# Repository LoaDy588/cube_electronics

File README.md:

# Cube Electronics

## Content

The repo currently contains KiCAD source files for the main board, interface board and a tiny sensor head.
It also includes all accompanying files, such as BOM.

## Building

The supplied `makefile` uses [KiKit](https://github.com/yaqwsx/KiKit) to automatically generate all output gerber files for JLCPCB.
Just run `make` in the top level directory to create all output gerbers and zip them in the `./gerber/` folder.

## 3D models, schematic symbols, footprints

This project relies on [LoaDy KiCAD Libs](https://github.com/LoaDy588/LoaDy_KiCAD_libs) for some footprints and the 3D models in the 3D preview on PCBNew

## License

The Main Board and Interface Board are licensed under CERN-OHL-W v2.

The MLX90393 sensor head is not licensed at all.

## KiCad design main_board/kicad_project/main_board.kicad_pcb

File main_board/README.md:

# Main Board

This is the main control board for Cube.

## Features
- powered by STM32G4 170MHz Cortex-M4 MCU
- four independent TMC2209 stepper drivers
- fully protected 10x limit switch inputs capable of 12V input
- USB communication with PC
- I2C and UART passthrough to MCU
- 3V3, 5V and 12V(supply) power rails

## License

Copyright Oldřich Pecák 2020.

This source describes Open Hardware and is licensed under the CERN-OHL-W v2.

You may redistribute and modify this source and make products using it under the terms of the CERN-OHL-S v2 (https://ohwr.org/cern_ohl_w_v2.txt).

This source is distributed WITHOUT ANY EXPRESS OR IMPLIED WARRANTY, INCLUDING OF MERCHANTABILITY, SATISFACTORY QUALITY AND FITNESS FOR A PARTICULAR PURPOSE. Please see the CERN-OHL-W v2 for applicable conditions.

Source location: LICENSE.txt

As per CERN-OHL-W v2 section 4, should You produce hardware based on this source, You must where practicable maintain the Source Location visible on the external case of the Gizmo or other products you make using this source.

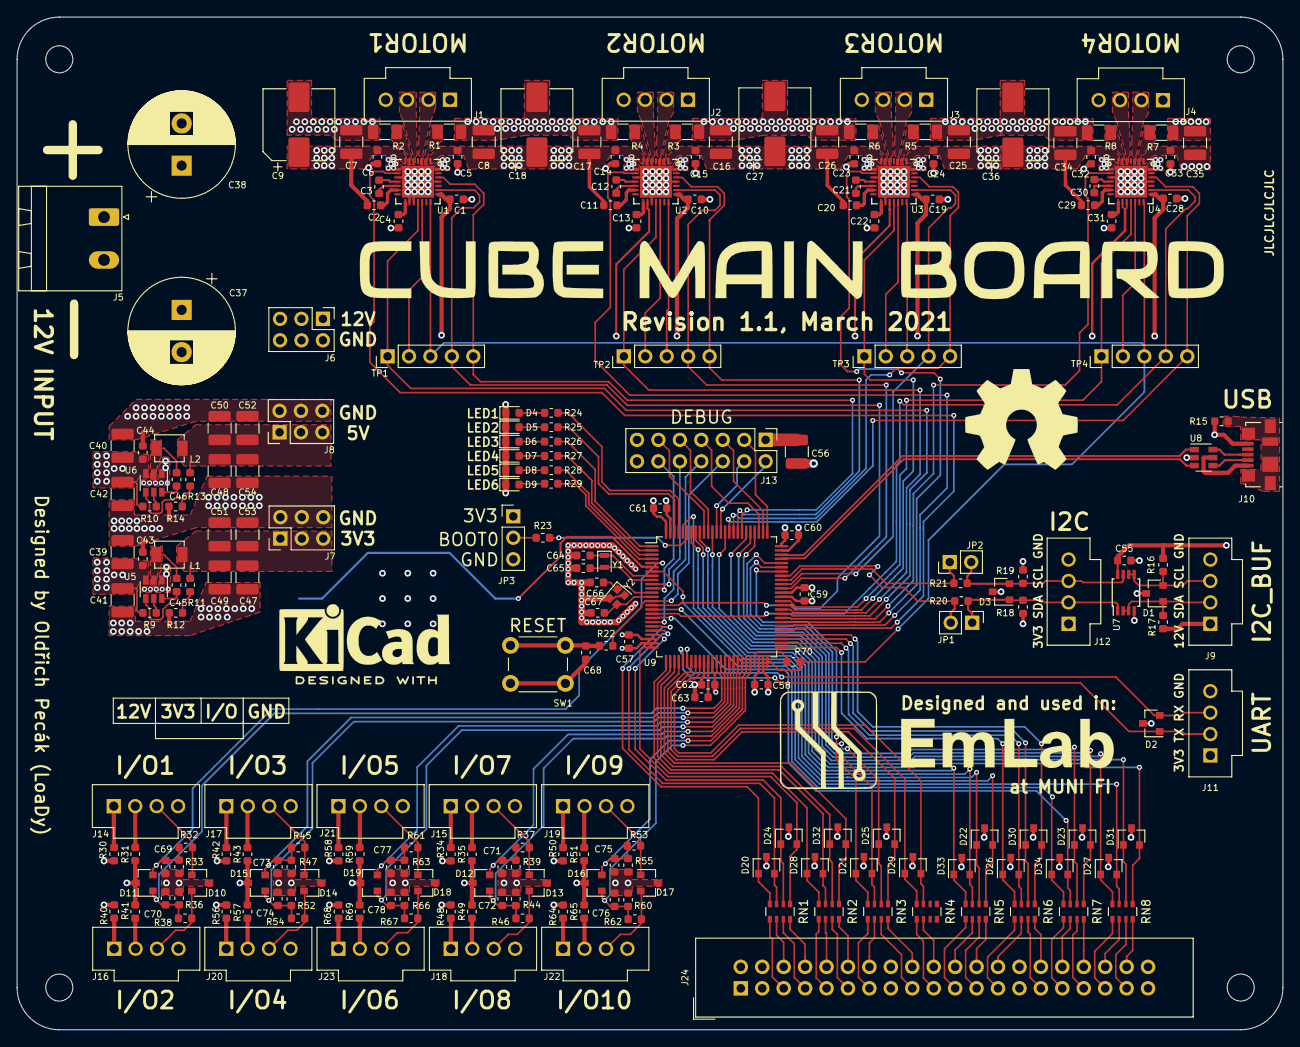
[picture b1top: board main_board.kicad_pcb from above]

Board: 4 copper layers, 150.0 x 120.0 mm, 236 parts (1 on the bottom side), 220 nets.

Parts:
BT1: CR2032; CR2032_SMD
C1, C2, C5, C6, C10, C11, C14, C15, C19, C20, C23, C24, C28, C29, C32, C33, C43, C44, C45, C46, C55, C57, C58, C59, C60, C61, C62, C63, C68: 100n; C_0603_1608Metric
C3, C12, C21, C30: 22n; C_0603_1608Metric
C4, C13, C22, C31: 2u2; C_0603_1608Metric
C7, C8, C16, C17, C25, C26, C34, C35, C39, C40, C41, C42, C47, C48, C49, C50, C51, C52, C53, C54, C56: 10u; C_1210_3225Metric
C9, C18, C27, C36: 100u; CP_Elec_8x10
C37, C38: 1m; CP_Radial_D12.5mm_P5.00mm
C64, C65: 12p5; C_0603_1608Metric
C66, C67: DNP; C_0603_1608Metric
C69, C70, C71, C72, C73, C74, C75, C76, C77, C78: 2n2; C_0603_1608Metric
D1: PESD12VS2UT; SOT-23
D2, D3, D10, D13, D14, D17, D18, D20, D21, D22, D23, D24, D25, D26, D27, D28, D29, D30, D31, D32, D33, D34: PESD3V3S2UT; SOT-23
D4, D5: LED_R; D_0603_1608Metric
D6, D7: LED_O; D_0603_1608Metric
D8, D9: LED_G; D_0603_1608Metric
D11, D12, D15, D16, D19: BAT54C; SOT-23
J1, J2, J3, J4: MOTOR; Molex_70543-0003
J5: PWR_ENTRY; PhoenixContact_MSTBA_2,5_2-G-5,08_1x02_P5.08mm_Horizontal
J6: 12V_HDR; PinHeader_2x03_P2.54mm_Vertical
J7: 3V3_HDR; PinHeader_2x03_P2.54mm_Vertical
J8: 5V_HDR; PinHeader_2x03_P2.54mm_Vertical
J9: I2C_BUFFERED; Molex_70543-0003
J10: USB_B_Micro; USB_Micro-B_Molex_47346-0001
J11: DATA_UART; Molex_70543-0003
J12: I2C_EXTERNAL; Molex_70543-0003
J13: DEBUG_HEADER; PinHeader_2x07_P2.54mm_Vertical
J14: IO1; Molex_70543-0003
J15: IO7; Molex_70543-0003
J16: IO2; Molex_70543-0003
J17: IO3; Molex_70543-0003
J18: IO8; Molex_70543-0003
J19: IO9; Molex_70543-0003
J20: IO4; Molex_70543-0003
J21: IO5; Molex_70543-0003
J22: IO10; Molex_70543-0003
J23: IO6; Molex_70543-0003
J24: EXPANSION_HEADER; IDC-Header_2x20_P2.54mm_Vertical
JP1: SDA_JMP; PinHeader_1x02_P2.54mm_Vertical
JP2: SCL_JMP; PinHeader_1x02_P2.54mm_Vertical
JP3: BOOT_SELECT; PinHeader_1x03_P2.54mm_Vertical
L1: 3u3; BOURNS_SRP3020TA
L2: 4u7; BOURNS_SRP3020TA
R1, R2, R3, R4, R5, R6, R7, R8: 150m; R_1206_3216Metric
R9, R10, R12, R14: 10K; R_0603_1608Metric
R11: 33K2; R_0603_1608Metric
R13: 54K9; R_0603_1608Metric
R15: 1M; R_0603_1608Metric
R16, R17: 2K2; R_0603_1608Metric
R18, R19, R32, R37, R38, R45, R46, R53, R54, R61, R62, R67: 4K7; R_0603_1608Metric
R20, R21: 0R; R_0603_1608Metric
R22: 150R; R_0603_1608Metric
R23, R24, R25, R26, R27, R28, R29, R30, R31, R34, R35, R40, R41, R42, R43, R48, R49, R50, R51, R56, R57, R58, R59, R64, R65, R68, R69, R70: 1K; R_0603_1608Metric
R33, R36, R39, R44, R47, R52, R55, R60, R63, R66: 47K; R_0603_1608Metric
RN1, RN2, RN3, RN4, RN5, RN6, RN7, RN8: 150R; R_Array_Convex_4x0603
SW1: SW_SPST; SW_PUSH_6mm_H5mm
TP1, TP2, TP3, TP4: DRIVER_TP; PinHeader_1x05_P2.54mm_Vertical
U1, U2, U3, U4: TMC2209; TMC2209-LA
U5, U6: TPS562200; SOT-23-6
U7: PCA9600DP; TSSOP-8_3x3mm_P0.65mm
U8: USBLC6-2SC6; SOT-23-6
U9: STM32G474VxT; LQFP-100_14x14mm_P0.5mm
Y1: ABS06-32.768kHz; Crystal_SMD_2012-2Pin_2.0x1.2mm
Y2: DNP; Crystal_SMD_2016-4Pin_2.0x1.6mm

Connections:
+3V3: C1.2, C10.2, C19.2, C28.2, C47.1, C49.1, C51.1, C53.1, C56.2, C57.2, C58.2, C59.2, C60.2, C61.2, C62.2, D11.3, D12.3, D15.3, D16.3, D19.3, J7.1, J7.3, J7.5, J11.1, J12.1, J13.1, J24.3, J24.4, JP3.1, L1.2, R11.1, R18.2, R19.2, R31.1, R35.1, R41.1, R43.1, R49.1, R51.1, R57.1, R59.1, R65.1, R69.1, U1.15, U2.9, U2.15, U3.10, U3.15, U4.9, U4.10, U4.15, U9.24, U9.37, U9.49, U9.64, U9.75, U9.100
+5V: C48.1, C50.1, C52.1, C54.1, J8.1, J8.3, J8.5, L2.2, R13.1
+12V: C2.2, C5.1, C6.1, C7.1, C8.1, C9.1, C11.2, C14.1, C15.1, C16.1, C17.1, C18.1, C20.2, C23.1, C24.1, C25.1, C26.1, C27.1, C29.2, C32.1, C33.1, C34.1, C35.1, C36.1, C37.1, C38.1, C39.1, C40.1, C41.1, C42.1, C43.1, C44.1, C55.1, J5.1, J6.1, J6.3, J6.5, J9.1, J24.1, J24.2, R9.2, R10.2, R16.2, R17.2, R30.1, R34.1, R40.1, R42.1, R48.1, R50.1, R56.1, R58.1, R64.1, R68.1, U1.22, U1.28, U2.22, U2.28, U3.22, U3.28, U4.22, U4.28, U5.3, U6.3, U7.8
/External I/O/DATA_UART_RX: D2.2, J11.3, U9.31
/External I/O/DATA_UART_TX: D2.1, J11.2, U9.30
/External I/O/I2C_SCL: JP2.1, R21.2, U9.67
/External I/O/I2C_SDA: JP1.2, R20.2, U9.68
/External I/O/USB_DATA_N: U8.3, U9.72
/External I/O/USB_DATA_P: U8.1, U9.73
/Limit Switches/IO1: C69.1, D11.2, R32.1, R33.2, U9.5
/Limit Switches/IO2: C70.2, D11.1, R36.2, R38.1, U9.38
/Limit Switches/IO3: C73.1, D15.2, R45.1, R47.2, U9.39
/Limit Switches/IO4: C74.2, D15.1, R52.2, R54.1, U9.40
/Limit Switches/IO5: C77.1, D19.2, R61.1, R63.2, U9.41
/Limit Switches/IO6: C78.2, D19.1, R66.2, R67.1, U9.42
/Limit Switches/IO7: C71.1, D12.2, R37.1, R39.2, U9.43
/Limit Switches/IO8: C72.2, D12.1, R44.2, R46.1, U9.44
/Limit Switches/IO9: C75.1, D16.2, R53.1, R55.2, U9.45
/Limit Switches/IO10: C76.2, D16.1, R60.2, R62.1, U9.46
/MCU/32_OSC_IN: C64.2, U9.8, Y1.1
/MCU/32_OSC_OUT: C65.2, U9.9, Y1.2
/MCU/BOOT0: R23.2, U9.95
/MCU/DEBUG_GPIO1: J13.8, U9.19
/MCU/DEBUG_GPIO2: J13.10, U9.10
/MCU/DEBUG_GPIO3: J13.12, U9.11
/MCU/DEBUG_LED1: R24.2, U9.97
/MCU/DEBUG_LED2: R25.2, U9.98
/MCU/DEBUG_LED3: R26.2, U9.1
/MCU/DEBUG_LED4: R27.2, U9.2
/MCU/DEBUG_LED6: R29.2, U9.4
/MCU/DEBUG_UART_RX: J13.4, U9.88
/MCU/DEBUG_UART_TX: J13.2, U9.87
/MCU/DEUBG_LED5: R28.2, U9.3
/MCU/EXP_IO1: D20.1, RN1.4, U9.20
/MCU/EXP_IO2: D20.2, RN1.3, U9.21
/MCU/EXP_IO3: D24.1, RN1.2, U9.22
/MCU/EXP_IO4: D24.2, RN1.1, U9.25
/MCU/EXP_IO5: D28.1, RN2.4, U9.26
/MCU/EXP_IO6: D28.2, RN2.3, U9.27
/MCU/EXP_IO7: D32.1, RN2.2, U9.28
/MCU/EXP_IO8: D32.2, RN2.1, U9.29
/MCU/EXP_IO9: D21.1, RN3.4, U9.69
/MCU/EXP_IO10: D21.2, RN3.3, U9.70
/MCU/EXP_IO11: D25.1, RN3.2, U9.71
/MCU/EXP_IO12: D25.2, RN3.1, U9.32
/MCU/EXP_IO13: D29.1, RN4.4, U9.33
/MCU/EXP_IO14: D29.2, RN4.3, U9.34
/MCU/EXP_IO15: D33.1, RN5.4, U9.92
/MCU/EXP_IO16: D33.2, RN5.3, U9.93
/MCU/EXP_IO17: D22.1, RN5.2, U9.94
/MCU/EXP_IO18: D22.2, RN5.1, U9.96
/MCU/EXP_IO19: D26.1, RN6.4, U9.51
/MCU/EXP_IO20: D26.2, RN6.3, U9.52
/MCU/EXP_IO21: D30.1, RN6.2, U9.53
/MCU/EXP_IO22: D30.2, RN6.1, U9.54
/MCU/EXP_IO23: D34.1, RN7.4, U9.16
/MCU/EXP_IO24: D34.2, RN7.3, U9.18
/MCU/EXP_IO25: D23.1, RN7.2, U9.79
/MCU/EXP_IO26: D23.2, RN7.1, U9.80
/MCU/EXP_IO27: D27.1, RN8.4, U9.81
/MCU/EXP_IO28: D27.2, RN8.3, U9.7
/MCU/EXP_IO29: D31.1, RN8.2, U9.86
/MCU/EXP_IO30: D31.2, RN8.1, U9.89
/MCU/HS_OSC_IN: C66.2, U9.12, Y2.1
/MCU/HS_OSC_OUT: C67.2, U9.13, Y2.3
/MCU/JDI: J13.7, U9.78
/MCU/JTDO_TRACESWO: J13.9, U9.90
/MCU/JTRST: J13.11, U9.91
/MCU/NRST: J13.6, R22.2, U9.14
/MCU/STEP_UART_RX: R70.2, TP1.3, TP2.3, TP3.3, TP4.3, U1.14, U2.14, U3.14, U4.14, U9.50
/MCU/STEP_UART_TX: R70.1, U9.47
/MCU/SWCLK_JTCK: J13.5, U9.77
/MCU/SWDIO_JTMS: J13.3, U9.76
/MCU/VREF: C63.2, U9.36
/STEP1/DIAG: TP1.1, U1.11, U9.59
/STEP1/DIR: TP1.5, U1.19, U9.82
/STEP1/ENABLE: U1.2, U9.55
/STEP1/INDEX: TP1.2, U1.12
/STEP1/STEP: TP1.4, U1.16, U9.15
/STEP2/DIAG: TP2.1, U2.11, U9.60
/STEP2/DIR: TP2.5, U2.19, U9.83
/STEP2/ENABLE: U2.2, U9.56
/STEP2/INDEX: TP2.2, U2.12
/STEP2/STEP: TP2.4, U2.16, U9.65
/STEP3/DIAG: TP3.1, U3.11, U9.61
/STEP3/DIR: TP3.5, U3.19, U9.84
/STEP3/ENABLE: U3.2, U9.57
/STEP3/INDEX: TP3.2, U3.12
/STEP3/STEP: TP3.4, U3.16, U9.66
/STEP4/DIAG: TP4.1, U4.11, U9.62
/STEP4/DIR: TP4.5, U4.19, U9.85
/STEP4/ENABLE: U4.2, U9.58
/STEP4/INDEX: TP4.2, U4.12
/STEP4/STEP: TP4.4, U4.16, U9.17
GND: BT1.2, C1.1, C4.2, C5.2, C6.2, C7.2, C8.2, C9.2, C10.1, C13.2, C14.2, C15.2, C16.2, C17.2, C18.2, C19.1, C22.2, C23.2, C24.2, C25.2, C26.2, C27.2, C28.1, C31.2, C32.2, C33.2, C34.2, C35.2, C36.2, C37.2, C38.2, C39.2, C40.2, C41.2, C42.2, C43.2, C44.2, C47.2, C48.2, C49.2, C50.2, C51.2, C52.2, C53.2, C54.2, C55.2, C56.1, C57.1, C58.1, C59.1, C60.1, C61.1, C62.1, C63.1, C64.1, C65.1, C66.1, C67.1, C68.1, C69.2, C70.1, C71.2, C72.1, C73.2, C74.1, C75.2, C76.1, C77.2, C78.1, D1.3, D2.3, D3.3, D4.1, D5.1, D6.1, D7.1, D8.1, D9.1, D10.3, D13.3, D14.3, D17.3, D18.3, D20.3, D21.3, D22.3, D23.3, D24.3, D25.3, D26.3, D27.3, D28.3, D29.3, D30.3, D31.3, D32.3, D33.3, D34.3, J5.2, J6.2, J6.4, J6.6, J7.2, J7.4, J7.6, J8.2, J8.4, J8.6, J9.4, J10.5, J11.4, J12.4, J13.13, J13.14, J14.4, J15.4, J16.4, J17.4, J18.4, J19.4, J20.4, J21.4, J22.4, J23.4, J24.15, J24.16, J24.27, J24.28, J24.39, J24.40, JP3.3, R1.1, R2.1, R3.1, R4.1, R5.1, R6.1, R7.1, R8.1, R12.2, R14.2, R15.1, R33.1, R36.1, R39.1, R44.1, R47.1, R52.1, R55.1, R60.1, R63.1, R66.1, SW1.2, U1.3, U1.9, U1.10, U1.18, U1.29, U2.3, U2.10, U2.18, U2.29, U3.3, U3.9, U3.18, U3.29, U4.3, U4.18, U4.29, U5.1, U6.1, U7.4, U8.2, U9.23, U9.35, U9.48, U9.63, U9.74, U9.99, Y2.2, Y2.4
unnamed: BT1.1, U9.6
unnamed: C2.1, U1.6
unnamed: C3.1, U1.5
unnamed: C3.2, U1.4
unnamed: C4.1, U1.8
unnamed: C11.1, U2.6
unnamed: C12.1, U2.5
unnamed: C12.2, U2.4
unnamed: C13.1, U2.8
unnamed: C20.1, U3.6
unnamed: C21.1, U3.5
unnamed: C21.2, U3.4
unnamed: C22.1, U3.8
unnamed: C29.1, U4.6
unnamed: C30.1, U4.5
unnamed: C30.2, U4.4
unnamed: C31.1, U4.8
unnamed: C45.1, L1.1, U5.2
unnamed: C45.2, U5.6
unnamed: C46.1, L2.1, U6.2
unnamed: C46.2, U6.6
unnamed: C68.2, R22.1, SW1.1
unnamed: D1.1, J9.2, R17.1, U7.2, U7.3
unnamed: D1.2, J9.3, R16.1, U7.5, U7.6
unnamed: D3.1, J12.2, JP1.1, R18.1, R20.1, U7.1
unnamed: D3.2, J12.3, JP2.2, R19.1, R21.1, U7.7
unnamed: D4.2, R24.1
unnamed: D5.2, R25.1
unnamed: D6.2, R26.1
unnamed: D7.2, R27.1
unnamed: D8.2, R28.1
unnamed: D9.2, R29.1
unnamed: D10.1, J14.3, R32.2
unnamed: D10.2, J16.3, R38.2
unnamed: D13.1, J15.3, R37.2
unnamed: D13.2, J18.3, R46.2
unnamed: D14.1, J17.3, R45.2
unnamed: D14.2, J20.3, R54.2
unnamed: D17.1, J19.3, R53.2
unnamed: D17.2, J22.3, R62.2
unnamed: D18.1, J21.3, R61.2
unnamed: D18.2, J23.3, R67.2
unnamed: J1.1, U1.21
unnamed: J1.2, U1.24
unnamed: J1.3, U1.26
unnamed: J1.4, U1.1
unnamed: J2.1, U2.21
unnamed: J2.2, U2.24
unnamed: J2.3, U2.26
unnamed: J2.4, U2.1
unnamed: J3.1, U3.21
unnamed: J3.2, U3.24
unnamed: J3.3, U3.26
unnamed: J3.4, U3.1
unnamed: J4.1, U4.21
unnamed: J4.2, U4.24
unnamed: J4.3, U4.26
unnamed: J4.4, U4.1
unnamed: J10.1, U8.5
unnamed: J10.2, U8.4
unnamed: J10.3, U8.6
unnamed: J10.6, R15.2
unnamed: J14.1, R30.2
unnamed: J14.2, R31.2
unnamed: J15.1, R34.2
unnamed: J15.2, R35.2
unnamed: J16.1, R40.2
unnamed: J16.2, R41.2
unnamed: J17.1, R42.2
unnamed: J17.2, R43.2
unnamed: J18.1, R48.2
unnamed: J18.2, R49.2
unnamed: J19.1, R50.2
unnamed: J19.2, R51.2
unnamed: J20.1, R56.2
unnamed: J20.2, R57.2
unnamed: J21.1, R58.2
unnamed: J21.2, R59.2
unnamed: J22.1, R64.2
unnamed: J22.2, R65.2
unnamed: J23.1, R68.2
unnamed: J23.2, R69.2
unnamed: J24.5, RN1.5
unnamed: J24.6, RN1.6
unnamed: J24.7, RN1.7
unnamed: J24.8, RN1.8
unnamed: J24.9, RN2.5
unnamed: J24.10, RN2.6
unnamed: J24.11, RN2.7
unnamed: J24.12, RN2.8
unnamed: J24.13, RN3.5
unnamed: J24.14, RN3.6
unnamed: J24.17, RN3.7
unnamed: J24.18, RN3.8
unnamed: J24.19, RN4.5
unnamed: J24.20, RN4.6
unnamed: J24.21, RN5.5
unnamed: J24.22, RN5.6
unnamed: J24.23, RN5.7
unnamed: J24.24, RN5.8
unnamed: J24.25, RN6.5
unnamed: J24.26, RN6.6
unnamed: J24.29, RN6.7
unnamed: J24.30, RN6.8
unnamed: J24.31, RN7.5
unnamed: J24.32, RN7.6
unnamed: J24.33, RN7.7
unnamed: J24.34, RN7.8
unnamed: J24.35, RN8.5
unnamed: J24.36, RN8.6
unnamed: J24.37, RN8.7
unnamed: J24.38, RN8.8
unnamed: JP3.2, R23.1
unnamed: R1.2, U1.23
unnamed: R2.2, U1.27
unnamed: R3.2, U2.23
unnamed: R4.2, U2.27
unnamed: R5.2, U3.23
unnamed: R6.2, U3.27
unnamed: R7.2, U4.23
unnamed: R8.2, U4.27
unnamed: R9.1, U5.5
unnamed: R10.1, U6.5
unnamed: R11.2, R12.1, U5.4
unnamed: R13.2, R14.1, U6.4

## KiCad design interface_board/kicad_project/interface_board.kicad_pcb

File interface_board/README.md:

# Interface Board

This board serves as a sensor interface on the moving head.

It includes power regulators, GPIO and two communication busses - I2C and SPI.

It communicates with the main board via buffered 12V I2C bus.

## License

Copyright Oldřich Pecák 2020.

This source describes Open Hardware and is licensed under the CERN-OHL-W v2.

You may redistribute and modify this source and make products using it under the terms of the CERN-OHL-W v2 (https://ohwr.org/cern_ohl_w_v2.txt).

This source is distributed WITHOUT ANY EXPRESS OR IMPLIED WARRANTY, INCLUDING OF MERCHANTABILITY, SATISFACTORY QUALITY AND FITNESS FOR A PARTICULAR PURPOSE. Please see the CERN-OHL-W v2 for applicable conditions.

Source location: LICENSE.txt

As per CERN-OHL-W v2 section 4, should You produce hardware based on this source, You must where practicable maintain the Source Location visible on the external case of the Gizmo or other products you make using this source.

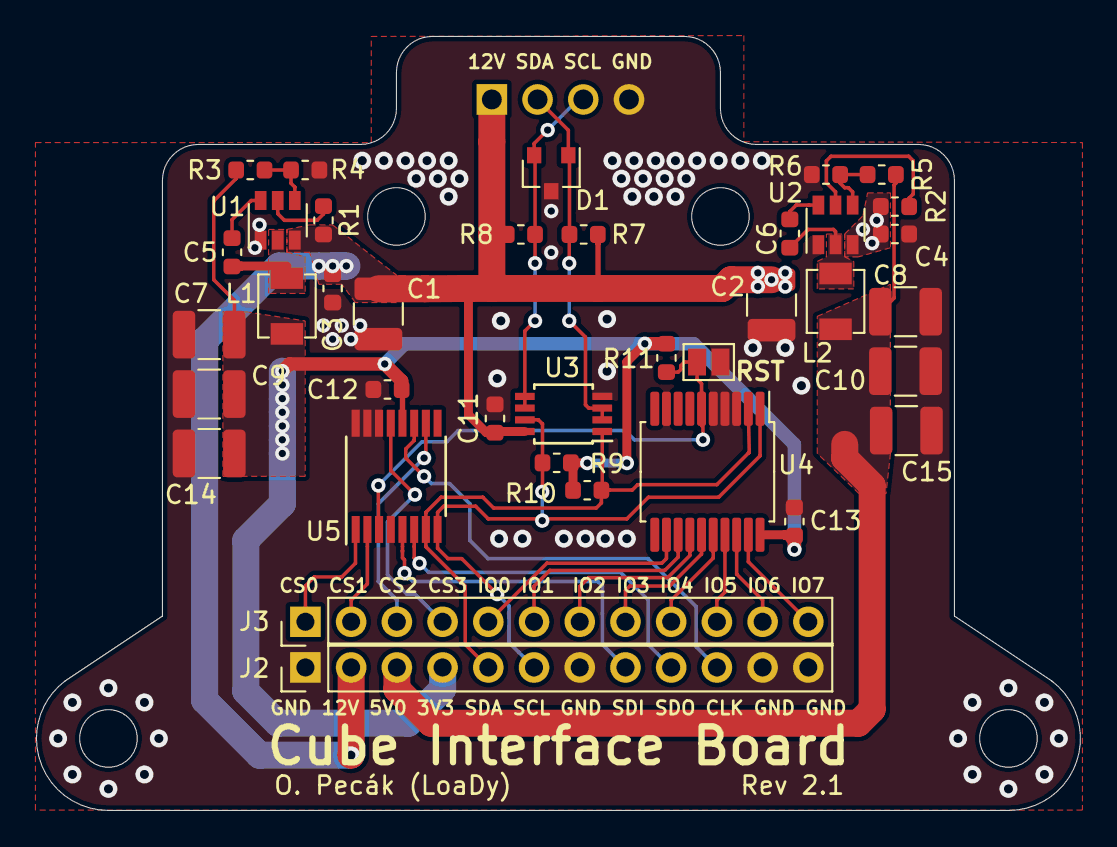
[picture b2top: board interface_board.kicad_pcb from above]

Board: 2 copper layers, 58.0 x 43.0 mm, 38 parts (1 on the bottom side), 32 nets.

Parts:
C1, C2, C7, C8, C9, C10, C14, C15: 10u; C_1210_3225Metric
C3, C4, C5, C6, C11, C12, C13: 100n; C_0603_1608Metric
D1: PESD12VS2UT; SOT-23
J1: INPUT; Molex_70543-0003
J2, J3: Conn_01x12; PinHeader_1x12_P2.54mm_Vertical
L1: 3u3; BOURNS_SRP3020TA
L2: 4u7; BOURNS_SRP3020TA
R1, R2, R4, R6: 10K; R_0603_1608Metric
R3: 33K2; R_0603_1608Metric
R5: 54K9; R_0603_1608Metric
R7, R8: 2K2; R_0603_1608Metric
R9, R10, R11: 4K7; R_0603_1608Metric
SW1: RESET; SolderJumper-2_P1.3mm_Open_Pad1.0x1.5mm
U1, U2: TPS563200; SOT-23-6
U3: PCA9600DP; TSSOP-8_3x3mm_P0.65mm
U4: MCP23008SS; SSOP-20_5.3x7.2mm_P0.65mm
U5: SC18IS602B; TSSOP-16_4.4x5mm_P0.65mm

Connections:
+3V3: C7.1, C9.1, C12.1, C13.1, C14.1, J2.4, L1.2, R3.1, R9.1, R10.1, R11.1, U4.20, U5.12
+5V: C8.1, C10.1, C15.1, J2.3, L2.2, R5.1
+12V: C1.1, C2.1, C3.1, C4.1, C11.1, J1.1, J2.2, R1.2, R2.2, R7.1, R8.1, U1.3, U2.3, U3.8
/I2C_SCL: J2.6, R9.2, U3.7, U4.1, U5.8
/I2C_SDA: J2.5, R10.2, U3.1, U4.2, U5.7
/RESET: R11.2, SW1.2, U4.6, U5.3
GND: C1.2, C2.2, C3.2, C4.2, C7.2, C8.2, C9.2, C10.2, C11.2, C12.2, C13.2, C14.2, C15.2, D1.3, J1.4, J2.1, J2.7, J2.11, J2.12, R4.2, R6.2, SW1.1, U1.1, U2.1, U3.4, U4.3, U4.4, U4.5, U4.9, U5.4, U5.14, U5.15, U5.16
unnamed: C5.1, U1.6
unnamed: C5.2, L1.1, U1.2
unnamed: C6.1, U2.6
unnamed: C6.2, L2.1, U2.2
unnamed: D1.1, J1.2, R7.2, U3.2, U3.3
unnamed: D1.2, J1.3, R8.2, U3.5, U3.6
unnamed: J2.8, U5.5
unnamed: J2.9, U5.6
unnamed: J2.10, U5.11
unnamed: J3.1, U5.1
unnamed: J3.2, U5.2
unnamed: J3.3, U5.10
unnamed: J3.4, U5.13
unnamed: J3.5, U4.12
unnamed: J3.6, U4.13
unnamed: J3.7, U4.14
unnamed: J3.8, U4.15
unnamed: J3.9, U4.16
unnamed: J3.10, U4.17
unnamed: J3.11, U4.18
unnamed: J3.12, U4.19
unnamed: R1.1, U1.5
unnamed: R2.1, U2.5
unnamed: R3.2, R4.1, U1.4
unnamed: R5.2, R6.1, U2.4

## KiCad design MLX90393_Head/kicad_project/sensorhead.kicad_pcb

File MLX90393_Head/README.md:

# MLX90393

This is a tiny carrier board for the MLX90393 sensor.

## BOM

- Melexis MLX90393 sensor, in QFN-16 package
- 2x: 100nF X7R MLCC capacitor, 0603 package (imperial)

## License

No license, as this is extremely simple board.

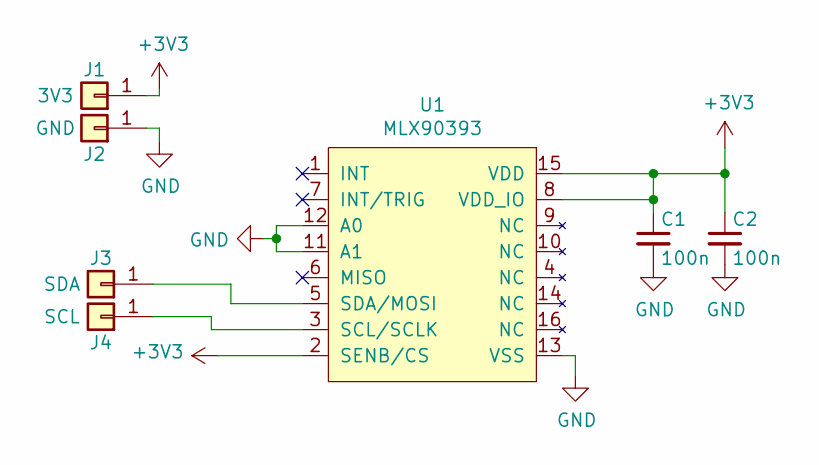
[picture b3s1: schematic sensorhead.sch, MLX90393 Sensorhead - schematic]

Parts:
C1, C2: 100n; C_0603_1608Metric
J1: 3V3; TestPoint_Pad_1.5x1.5mm
J2: GND; TestPoint_Pad_1.5x1.5mm
J3: SDA; TestPoint_Pad_1.5x1.5mm
J4: SCL; TestPoint_Pad_1.5x1.5mm
U1: MLX90393; QFN-16-1EP_3x3mm_P0.5mm_EP1.75x1.75mm

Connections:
+3V3: C1.1, C2.1, J1.1, U1.2 (SENB/CS), U1.8 (VDD_IO), U1.15 (VDD)
GND: C1.2, C2.2, J2.1, U1.11 (A1), U1.12 (A0), U1.13 (VSS), U1.17 (PAD)
unnamed: J3.1, U1.5 (SDA/MOSI)
unnamed: J4.1, U1.3 (SCL/SCLK)

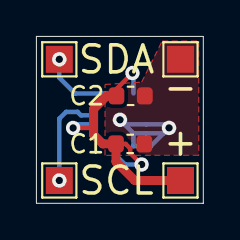
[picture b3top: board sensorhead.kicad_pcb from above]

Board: 2 copper layers, 9.3 x 9.3 mm, 7 parts (1 on the bottom side), 4 nets.

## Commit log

2020-08-31 start repo, add interface board
2020-08-31 add basic readmes
2020-08-31 add start of main board
2020-08-31 add MLX90393 sensor head
2020-08-31 add power to main board
2020-09-01 add readmes, add MCU to main board, update footprints on interface board
2020-09-02 add input/output schematic, add documentation
2020-09-08 Fix I/O protection
2020-09-08 rename sheets
2020-09-08 remove old file
2020-09-08 add external IO
2020-09-08 actually add external IO
2020-09-10 add input protection to interface board
2020-09-15 interface board add new connector and edit layout
2020-09-21 progress?
2020-09-22 progress on MCU pinout
2020-09-22 more progress on MCU pinout
2020-09-22 fix bus connection
2020-09-23 MCU pinout done
2020-09-23 schematic rev1 finished
2020-09-24 main board: layout start, steppers done
2020-09-24 edits to stepper layout
2020-09-25 regulators layout done
2020-09-26 limit switch layout
2020-09-26 expansion connector - rev 1.1 schematic, finished layout
2020-09-27 external IO layout WIP, small chances to external IO schematic
2020-09-28 routing half finished
2020-09-28 routing finished
2020-09-28 add graphics
2020-10-10 Main board sch: add backup battery, update license
2020-10-18 change connector for interface board, edit silkscreen layers for interface and main boards
2020-10-19 change oshw logo pos on mainboard
2020-10-19 add interface board silkscreen, modify main board silkscreen
2020-10-19 edit READMEs, add LICENCE.txt
2020-10-19 add BOMs
2020-10-19 update TMC2209 footprints on main board
2020-10-23 change folder names, add makefile
2020-10-24 fix .gitignore, slight makefile changes
2020-10-24 fix lincense notices in READMEs
2021-03-13 change resistor network package
2021-11-03 update readme, add license

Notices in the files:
parts and their libraries:
Copyright 2016 Accelerated Designs. All rights reserved.
